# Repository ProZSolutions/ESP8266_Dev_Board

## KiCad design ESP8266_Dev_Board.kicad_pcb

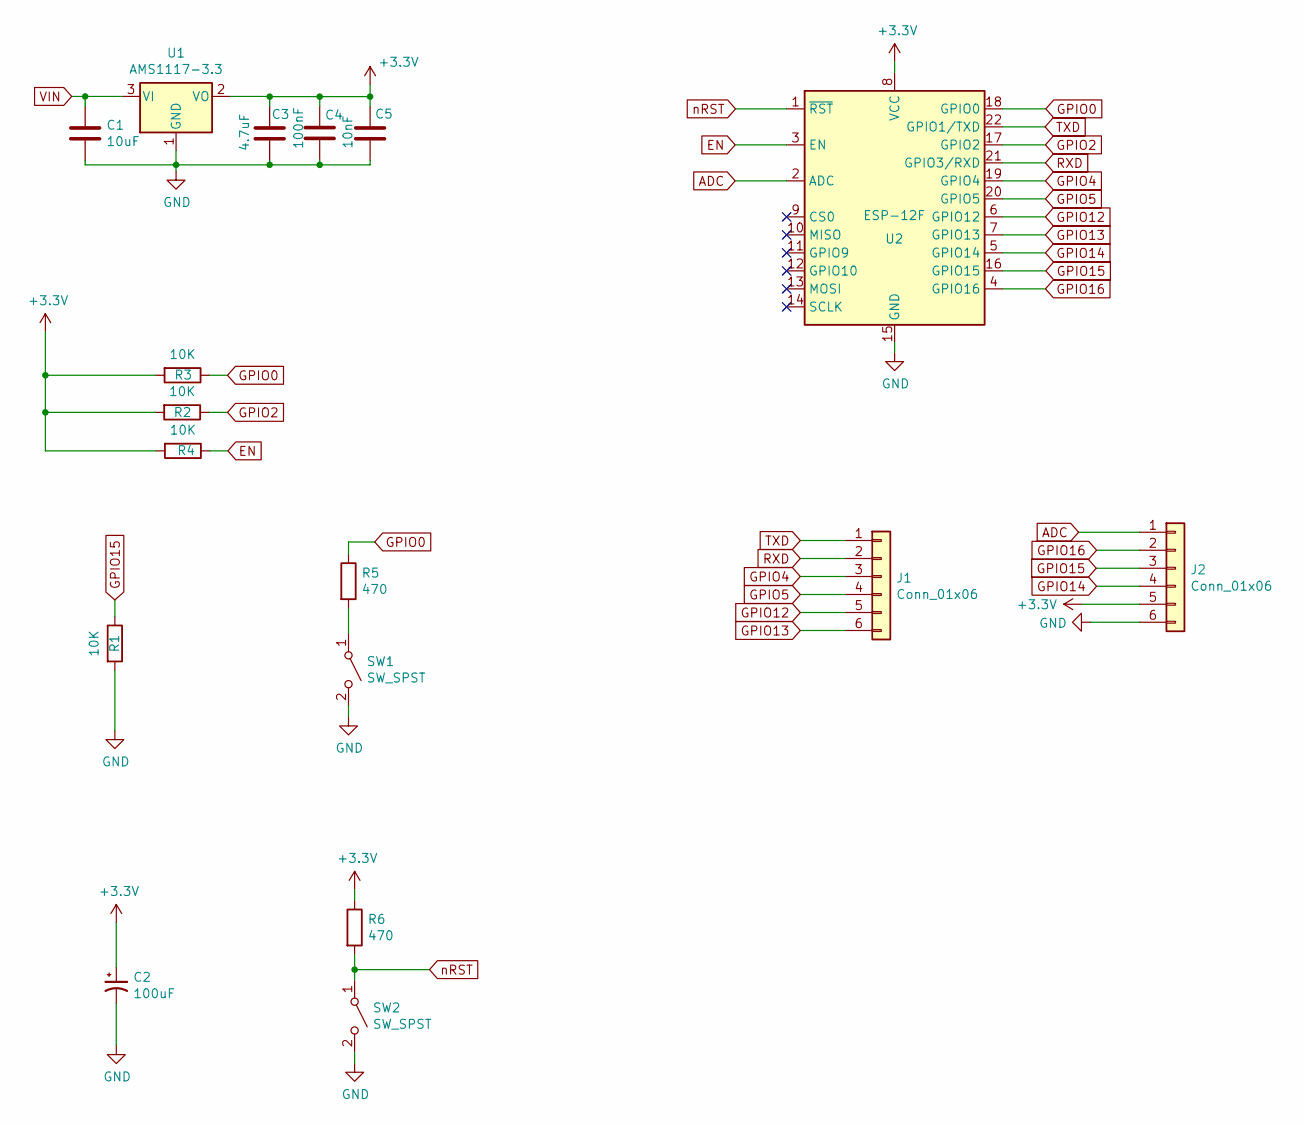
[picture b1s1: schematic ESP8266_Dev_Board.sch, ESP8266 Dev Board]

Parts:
C1: 10uF; C_0805_2012Metric_Pad1.18x1.45mm_HandSolder
C2: 100uF; CP_EIA-7343-15_Kemet-W_Pad2.25x2.55mm_HandSolder
C3: 4.7uF; C_0805_2012Metric_Pad1.18x1.45mm_HandSolder
C4: 100nF; C_0805_2012Metric_Pad1.18x1.45mm_HandSolder
C5: 10nF; C_0805_2012Metric_Pad1.18x1.45mm_HandSolder
J1, J2: Conn_01x06; PinHeader_1x06_P2.00mm_Vertical
R1, R2, R3, R4: 10K; R_0805_2012Metric_Pad1.20x1.40mm_HandSolder
R5, R6: 470; R_0603_1608Metric_Pad0.98x0.95mm_HandSolder
SW1, SW2: SW_SPST; SW_SPST_CK_RS282G05A3
U1: AMS1117-3.3; SOT-223-3_TabPin2
U2: ESP-12F; ESP-12E

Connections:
+3V3: C2.1, C3.1, C4.1, C5.1, J2.5, R2.2, R3.2, R4.2, R6.1, U1.2 (VO), U2.8 (VCC)
ADC: J2.1, U2.2 (ADC)
EN: R4.1, U2.3 (EN)
GND: C1.2, C2.2, C3.2, C4.2, C5.2, J2.6, R1.2, SW1.2 (B), SW2.2 (B), U1.1 (GND), U2.15 (GND)
GPIO0: R3.1, R5.1, U2.18 (GPIO0)
GPIO2: R2.1, U2.17 (GPIO2)
GPIO4: J1.3, U2.19 (GPIO4)
GPIO5: J1.4, U2.20 (GPIO5)
GPIO12: J1.5, U2.6 (GPIO12)
GPIO13: J1.6, U2.7 (GPIO13)
GPIO14: J2.4, U2.5 (GPIO14)
GPIO15: J2.3, R1.1, U2.16 (GPIO15)
GPIO16: J2.2, U2.4 (GPIO16)
unnamed: R5.2, SW1.1 (A)
RXD: J1.2, U2.21 (GPIO3/RXD)
TXD: J1.1, U2.22 (GPIO1/TXD)
VIN: C1.1, U1.3 (VI)
nRST: R6.2, SW2.1 (A), U2.1 (~RST)

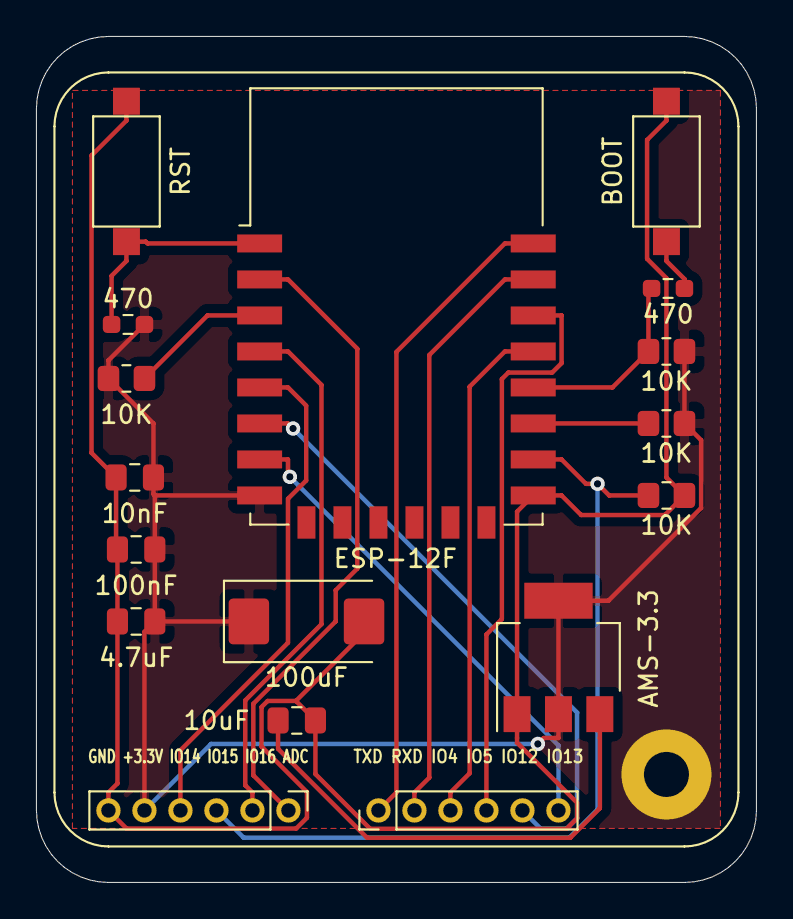
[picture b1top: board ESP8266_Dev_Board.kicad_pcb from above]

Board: 2 copper layers, 40.0 x 47.0 mm, 17 parts (0 on the bottom side), 18 nets.
